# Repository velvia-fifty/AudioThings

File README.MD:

# AudioThings

<div style="display: flex; flex-direction: row;">
 &nbsp;&nbsp;
 &nbsp;&nbsp;  &nbsp;&nbsp; 
</div>

<sup>*I made this for me, maybe you find it helpful?*</sup>

>What is the meaning of life? Are we here only to eat hot chip, shitpost, and make the robot have orgasm?
>
>**No!**
>
>*We do audio, we do thing, we do audio things!*

## Getting the most out of your trip to Cleveland Ohio

When you download this as a ZIP open AudioThings.kicad_pro, this is a panopticon project that contains the main resources and exists to handle some references that are common. Apparently KiCad and I have some foundational disagreement on how to misuse their software; this is primarily because I'm ignorant, but also they have incorrect opinions.

Use Kicad to drill down into other projects.

Or don't, I'm not a cop.

## F.A.Q.

1. Are you OK?
2. Seriously I'm concerned for your wellbeing, is everything alright at home?

🤫

## Navigating this hot mess of a repo

This repo is poorly organized and so am I, here are the main non-project folders.

- [Art](./Art/)
  - Less-than-practical boards that are incomplete.
- [CRIB SHEET](./CRIB%20SHEET/)
  - Things I ~stole~ used for inspiration.
- [docs](./docs/)
  - Audio Things: The Manual: The Webpage: The Source
- [Modules](./Modules/)
  - The stuff that's mostly complete
- [OLD](./OLD/)
  - The trashcan, I sometimes use this to store things
- [res](./res/)
  - Central resource folder containing footprints, 3d models, and other assets.
  - Referenced at ${KIPROJMOD}/../../res/
- [Tools](./Tools/)
  - Hammers, Templates, etc.
- [Workshop](./Workshop/)
  - Half-baked and half-finished boards

### Project Resources

Footprint Library
${KIPRJMOD}/../../res/AT-Footprints.pretty

## I have opinions and they're loud

Opinions are for suckers, we're a big girl, we have convictions (and they're obtuse).

### Maximize Cheap

If we wanted to spend money, we wouldn't pay with our time!

- Boards stay within 100mm x 100mm to get the cheapest per-board costs for small orders
- BOM includes actively produced parts unless there are no other options
- Rely on someone else's scale and use the most common solution in the wrong way

See: [Fab Min-Max Notes](./FAB_NOTES.MD)

### Form Factor Agnostic

- Assume Eurorack
- Assume Backplane
- Assume Stacking
- Assume Standalone

### Your Licensing Model is Bad and You Should Feel Bad

- All work is under copyright, this is not antithetical to the concept of the public domain
  - I mean *all* work, not just this repo.
- What I'm offering is licensed to you under [Creative Commons Attribution-NonCommercial-ShareAlike 4.0 International](https://creativecommons.org/licenses/by-nc-sa/4.0/)
- If you're not an individual, the words "copyright" and "NonCommercial" are very important to both you, me, and a lawyer makes three.
  - Corporations don't have rights.

For how I really feel, see: [LICENSE.MD](./LICENSE.MD)

## Core Features

- Eurorack Compatible
- Backplane preferred but optional
- Daughterboards are assumed (Minium PCB order is 5 after all)

# I took notes here, don't look

m.2
<https://github.com/timonsku/M.2-Card-Footprints/tree/main>

# Universal Faceplate

Universal 6mm opening for jacks and pots

11.5mm between board and face

SJ3-350103A 3.5mm Stereo
<https://www.digikey.com/en/products/detail/same-sky-formerly-cui-devices/SJ3-350103A/24627980>

PTV09 Pots
<https://www.bourns.com/docs/Product-Datasheets/PTV09.pdf>

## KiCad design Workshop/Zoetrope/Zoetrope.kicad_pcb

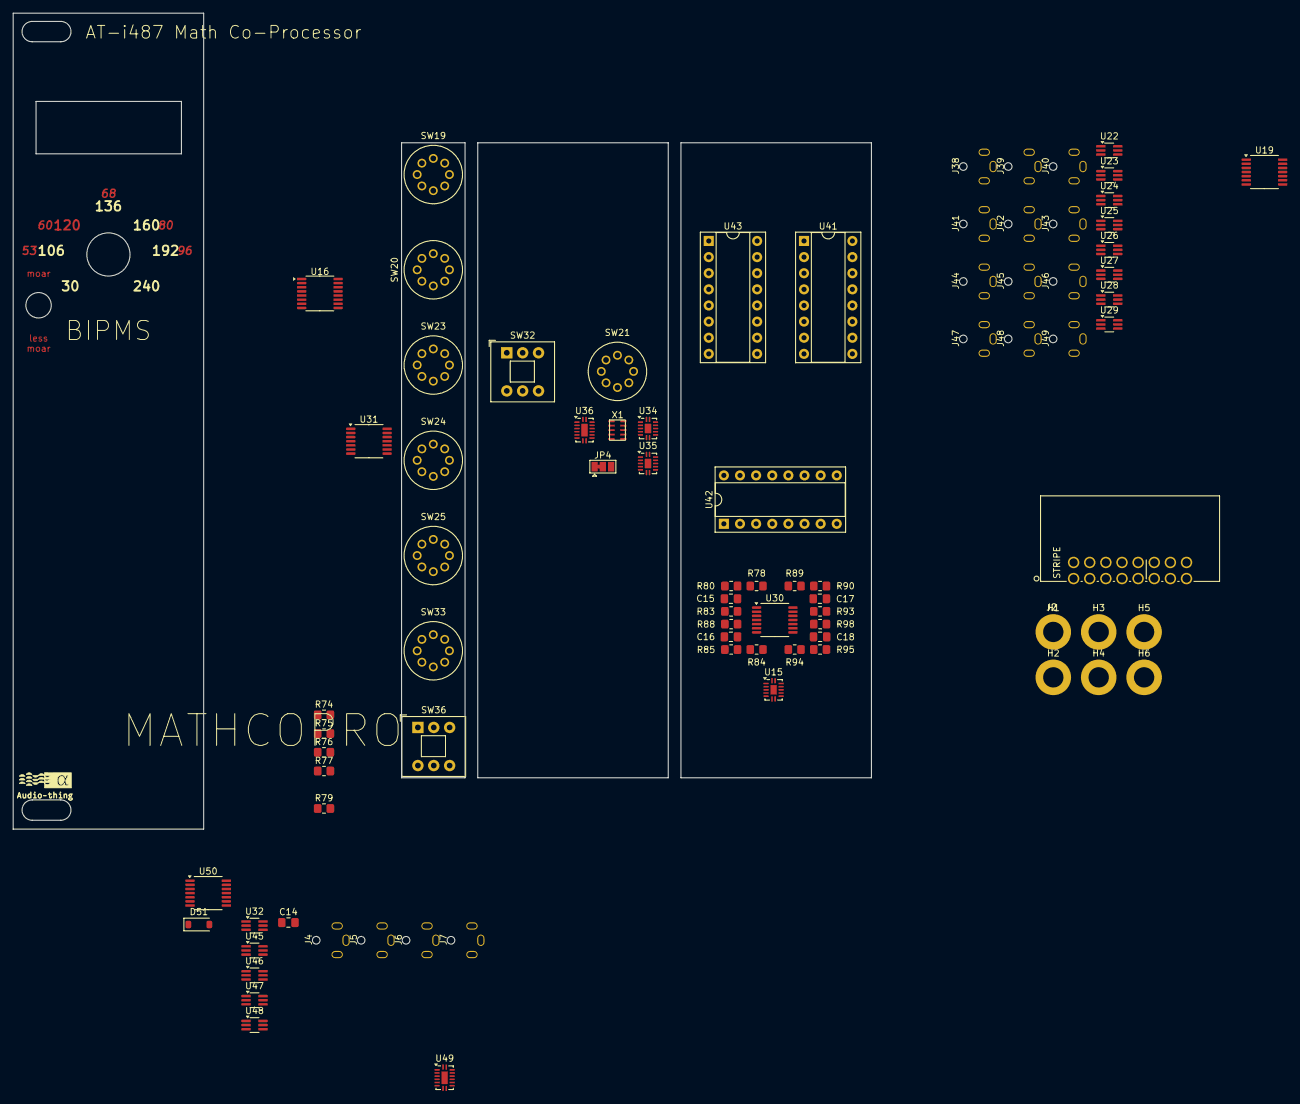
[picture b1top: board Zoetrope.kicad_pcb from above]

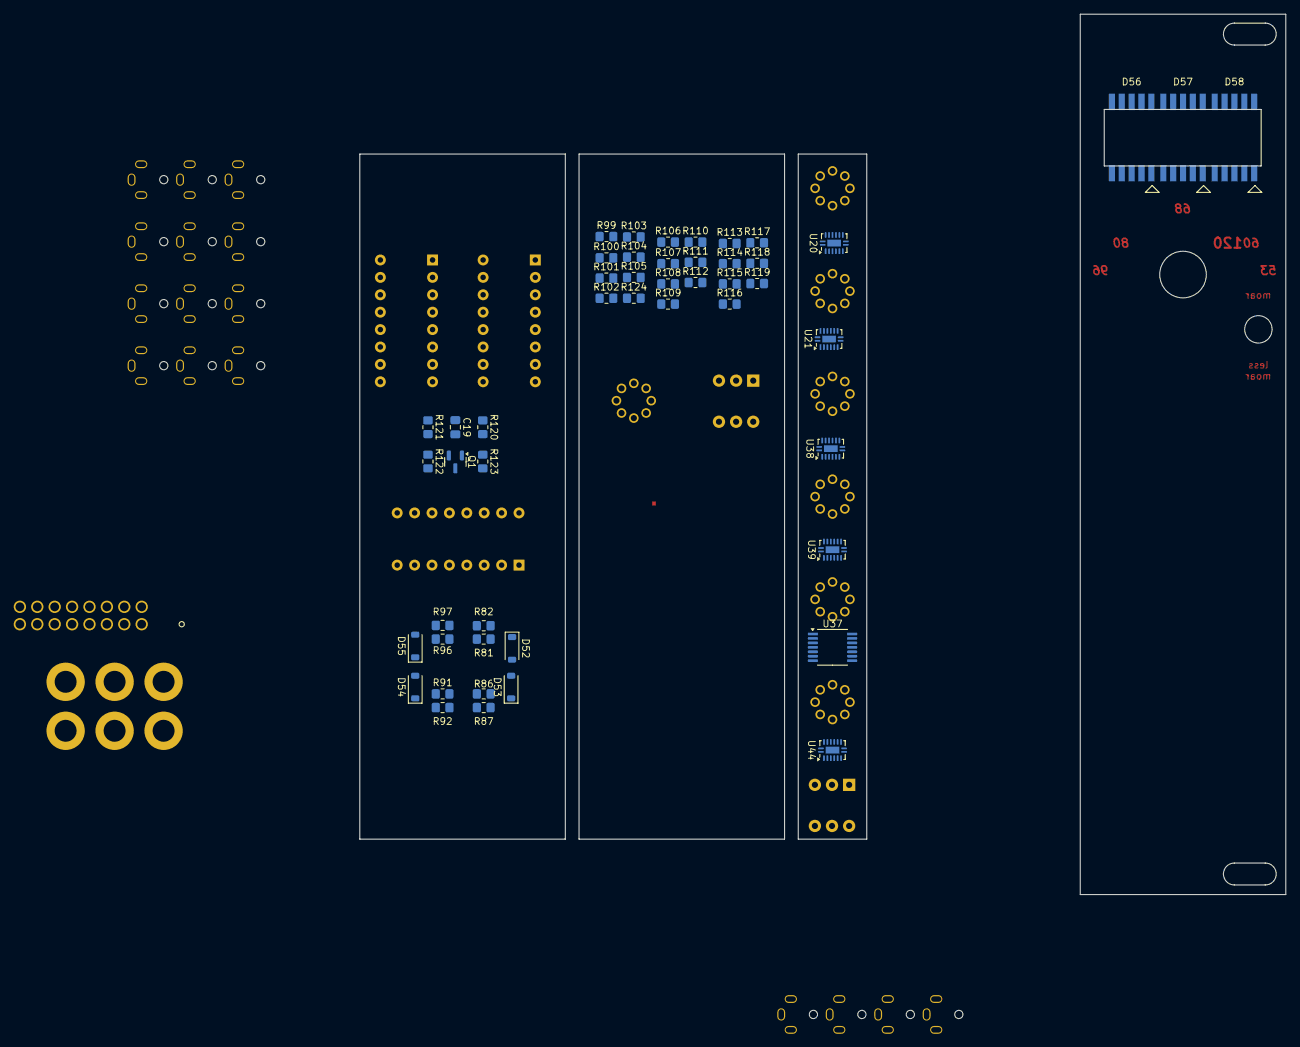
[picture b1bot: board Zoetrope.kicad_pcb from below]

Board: 2 copper layers, 164.4 x 146.6 mm, 132 parts (46 on the bottom side), 159 nets, no tracks yet.

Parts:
C14, C15, C16, C17, C18: 10nf; C_0805_2012Metric_Pad1.18x1.45mm_HandSolder
C19: 100nf; C_0805_2012Metric_Pad1.18x1.45mm_HandSolder
D51, D52, D53, D54, D55: 1N4148W; D_SOD-123
D56: BPM DISP Ones; Reverse Mount WL-S7DS_0.2INCH
D57: BPM DISP Tens; Reverse Mount WL-S7DS_0.2INCH
D58: BPM DISP Hundreds; Reverse Mount WL-S7DS_0.2INCH
H1, H2, H3, H4, H5, H6: M3; MountingHole_3.2mm_M3_DIN965_Pad
J2: OPT EURO; EURORACK Right Angle
J4: Bar End Trigger; SJ3
J5: Beat Clock Out; SJ3
J6: Phrase End Trigger; SJ3
J7: Gate In - Bank A; SJ3
J38: 1/2 Trigger; SJ3
J39: 1/4 Trigger; SJ3
J40: 1/8 Trigger; SJ3
J41: 1/16 Trigger; SJ3
J42: 1/2 Front Gate; SJ3
J43: 1/4 Front Gate; SJ3
J44: 1/8 Front Gate; SJ3
J45: 1/16 Front Gate; SJ3
J46: 1/2 Back Gate; SJ3
J47: 1/4 Back Gate; SJ3
J48: 1/8 Back Gate; SJ3
J49: 1/16 Back Gate; SJ3
JP4: SET BPM Upper; SolderJumper-3_P1.3mm_Bridged12_Pad1.0x1.5mm
Q1: MMBT2222A; SOT-23
R74, R77, R78, R83, R84, R88, R89, R93, R94, R98: 100k; R_0805_2012Metric_Pad1.20x1.40mm_HandSolder
R75, R81, R86, R91, R96: 2.7k; R_0805_2012Metric_Pad1.20x1.40mm_HandSolder
R76, R82, R87, R92, R97: 2.2k; R_0805_2012Metric_Pad1.20x1.40mm_HandSolder
R79, R80, R85, R90, R95, R121: 1k; R_0805_2012Metric_Pad1.20x1.40mm_HandSolder
R99, R100, R101, R102, R103, R104, R105, R106, R107, R108, R109, R110, R111, R112, R113, R114, R115, R116, R117, R118, R119, R124: 150R; R_0805_2012Metric_Pad1.20x1.40mm_HandSolder
R120: 3k3; R_0805_2012Metric_Pad1.20x1.40mm_HandSolder
R122: 20k; R_0805_2012Metric_Pad1.20x1.40mm_HandSolder
R123: 2k; R_0805_2012Metric_Pad1.20x1.40mm_HandSolder
SW19: Bar Length _{Coarse}; RM-SWITCH
SW20, SW23, SW24, SW25: Bar Length _{Cont}; RM-SWITCH
SW21: BPM _{Coarse}; RM-SWITCH
SW32: BPM Range; SW_Push_2P2T_Toggle_CK_PVA2OAH5xxxxxxV2
SW33: Phrase Length; RM-SWITCH
SW36: Single Bar; SW_Push_2P2T_Toggle_CK_PVA2OAH5xxxxxxV2
U15, U34, U35: NEX 74HC393BQ,115; DHVQFN-14-1EP_2.5x3mm_P0.5mm_EP1x1.5mm
U16: 40106; TSSOP-16_4.4x5mm_P0.65mm
U19, U37, U50: 74HC08; TSSOP-14_4.4x5mm_P0.65mm
U20, U21, U36, U38, U39, U44, U49: 4017; DHVQFN-16-1EP_2.5x3.5mm_P0.5mm_EP1x2mm
U22, U23, U24, U25, U26, U27, U28, U29, U32, U45, U46, U47, U48: 74LVC1G3157; SOT-363_SC-70-6_Handsoldering
U30, U31: TL074; TSSOP-14_4.4x5mm_P0.65mm
U41, U42, U43: 40110; DIP-16_W7.62mm_Socket
X1: TG-3541CE

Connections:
1 Count: U20.3 (Q0), U21.15 (Reset)
2 Count: SW19.2, U20.2 (Q1), U22.3
3 Count: SW19.3, U20.4 (Q2), U23.3
4 Count: SW19.1, U20.7 (Q3), U24.3
5 Count: SW20.1, U19.5, U20.10 (Q4), U25.3
6 Count: SW19.4, U20.1 (Q5), U29.3
7 Count: SW20.2, U19.6, U20.5 (Q6), U28.3
8 Count: U20.6 (Q7), U27.3
9 Count: SW19.5, U20.9 (Q8), U26.3
10 Count: SW20.3, U21.2 (Q1), U22.1
11 Count: SW20.4, U21.4 (Q2), U23.1
12 Count: SW19.6, U21.7 (Q3), U24.1
13 Count: SW23.1, U21.10 (Q4), U25.1
14 Count: SW23.2, U21.1 (Q5), U29.1
15 Count: SW23.3, U21.5 (Q6), U28.1
16 Count: SW23.4, U21.6 (Q7), U27.1
16th Trigger: J41.T, R96.2, R97.2
17 Count: SW23.5, U21.9 (Q8), U26.1
18 Count: SW23.6, U38.2 (Q1)
19 Count: SW23.7, U38.4 (Q2)
20 Count: SW24.1, U38.7 (Q3)
21 Count: SW24.2, U38.10 (Q4)
22 Count: SW24.3, U38.1 (Q5)
23 Count: SW24.4, U38.5 (Q6)
24 Count: SW24.5, U38.6 (Q7)
25 Count: SW24.6, U38.9 (Q8)
27 Count: SW25.1, U39.4 (Q2)
28 Count: SW25.2, U39.7 (Q3)
29 Count: SW25.3, U39.10 (Q4)
30 Count: SW25.4, U39.1 (Q5)
30_{BPM}: C19.2, R120.2, R123.1, SW21.7, U35.8 (Q3), U41.6 (LE), U42.6 (LE), U43.6 (LE)
31 Count: SW25.5, U39.5 (Q6)
32 Count: SW25.6, U39.6 (Q7)
33 Count: SW25.7, U39.9 (Q8)
106_{BPM}: SW21.6, U36.9 (Q8)
120_{BPM}: JP4.1 (A), SW21.5, U35.9 (Q2), U35.10 (Q1), U36.6 (Q7)
137_{BPM}: SW21.4, U36.5 (Q6)
160_{BPM}: SW21.3, U36.1 (Q5)
192_{BPM}: SW21.2, U36.10 (Q4)
240_{BPM}: JP4.3 (B), U35.11 (Q0)
+5V: J2.11, J2.12, U15.14 (VCC), U20.16 (VDD), U21.16 (VDD), U34.14 (VCC), U35.14 (VCC), U36.16 (VDD), U38.16 (VDD), U39.16 (VDD), U41.16 (Vdd), U42.16 (Vdd), U43.16 (Vdd), U44.16 (VDD), U49.16 (VDD), X1.1 (OE), X1.2 (VCC), X1.3 (VCC)
+12V: J2.9, J2.10
+12v: R78.2, R84.2, R89.2, R94.2
-12V: J2.1, J2.2
/Bus/CON_CV: J2.13, J2.14
/Bus/CON_GATE: J2.15, J2.16
/SEQ/2.048k Clock: U34.6 (Q3), U34.13 (CP)
/SEQ/8Hz Clock: SW32.3 (C), U35.6 (Q3), U35.13 (CP)
/SEQ/16Hz Clock: SW32.1 (A), U35.5 (Q2)
/SEQ/32.768k Clock: U34.1 (CP), X1.4 (OUT)
/SEQ/128Hz Clock: SW32.6 (C), U34.8 (Q3), U35.1 (CP)
/SEQ/256Hz Clock: SW32.4 (A), U34.9 (Q2)
/SEQ/A1: R99.1, U41.1 (Qa)
/SEQ/A2: R106.1, U42.1 (Qa)
/SEQ/A3: R113.1, U43.1 (Qa)
/SEQ/B1: R100.1, U41.15 (Qb)
/SEQ/B2: R107.1, U42.15 (Qb)
/SEQ/B3: R114.1, U43.15 (Qb)
/SEQ/BPM DISP Clock: Q1.2 (E), R122.2, R124.1, U41.9 (CKu), U42.9 (CKu), U43.9 (CKu)
/SEQ/BPM DISP Reset: C19.1, R121.2, U41.5 (CLR), U42.5 (CLR), U43.5 (CLR)
/SEQ/C1: R101.1, U41.14 (Qc)
/SEQ/C2: R108.1, U42.14 (Qc)
/SEQ/C3: R115.1, U43.14 (Qc)
/SEQ/D1: R102.1, U41.13 (Qd)
/SEQ/D2: R109.1, U42.13 (Qd)
/SEQ/D3: R116.1, U43.13 (Qd)
/SEQ/E1: R103.1, U41.12 (Qe)
/SEQ/E2: R110.1, U42.12 (Qe)
/SEQ/E3: R117.1, U43.12 (Qe)
/SEQ/F1: R104.1, U41.3 (Qf)
/SEQ/F2: R111.1, U42.3 (Qf)
/SEQ/F3: R118.1, U43.3 (Qf)
/SEQ/G1: R105.1, U41.2 (Qg)
/SEQ/G2: R112.1, U42.2 (Qg)
/SEQ/G3: R119.1, U43.2 (Qg)
Bank A - Position: U45.6, U46.6, U47.6, U48.6
Bar: J4.T, SW19.8, U20.15 (Reset), U39.11 (Q9), U44.14 (CLK)
Beat: J5.T, Q1.3 (C), SW21.8, U20.14 (CLK), U36.15 (Reset)
Eighth Bar: SW33.6, U44.6 (Q7)
Eighth Note A: C17.1, J44.T, J48.T, U15.4 (Q1), U15.10 (Q1), U46.1, U46.3
Eighth Tigger: J40.T, R91.2, R92.2
Fifth Bar: SW33.3, U44.10 (Q4)
Fourth Bar: SW33.2, U44.7 (Q3)
GND: D56.3, D57.3, D58.3, J2.3, J2.4, J2.5, J2.6, J2.7, J2.8, J4.S, J5.S, J6.S, J7.S, J38.S, J39.S, J40.S, J41.S, J42.S, J43.S, J44.S, J45.S, J46.S, J47.S, J48.S, J49.S, R74.2, R76.1, R79.1, R80.1, R82.1, R83.1, R85.1, R87.1, R88.1, R90.1, R92.1, R93.1, R95.1, R97.1, R98.1, R120.1, R121.1, R122.1, U15.2 (MR), U15.7 (GND), U15.12 (MR), U20.8 (VSS), U21.8 (VSS), U21.13 (CKEN), U34.2 (MR), U34.7 (GND), U34.12 (MR), U35.2 (MR), U35.7 (GND), U35.12 (MR), U36.8 (VSS), U36.13 (CKEN), U38.8 (VSS), U38.13 (CKEN), U39.8 (VSS), U39.13 (CKEN), U41.4 (~TE), U41.7 (CKd), U41.8 (Vss), U42.4 (~TE), U42.7 (CKd), U42.8 (Vss), U43.4 (~TE), U43.7 (CKd), U43.8 (Vss), U44.8 (VSS), U44.13 (CKEN), U49.8 (VSS), U49.13 (CKEN), X1.5 (GND), X1.7 (GND), X1.8 (GND), X1.9 (GND)
Half Note A: C14.1, C15.1, J42.T, J46.T, U15.6 (Q3), U15.8 (Q3), U48.1, U48.3
Half Trigger: J38.T, R81.2, R82.2
unnamed: D51.2 (A), U31.7
unnamed: D51.1 (K), R75.1
unnamed: D52.2 (A), U30.1
unnamed: D52.1 (K), R81.1
unnamed: D53.2 (A), U30.7
unnamed: D53.1 (K), R86.1
unnamed: D54.2 (A), U30.8
unnamed: D54.1 (K), R91.1
unnamed: D55.2 (A), U30.14
unnamed: D55.1 (K), R96.1
unnamed: D56.1, R103.2
unnamed: D56.2, R102.2
unnamed: D56.4, R101.2
unnamed: D56.5, R124.2
unnamed: D56.6, R100.2
unnamed: D56.7, R99.2
unnamed: D56.9, R104.2
unnamed: D56.10, R105.2
unnamed: D57.1, R110.2
unnamed: D57.2, R109.2
unnamed: D57.4, R108.2
unnamed: D57.6, R107.2
unnamed: D57.7, R106.2
unnamed: D57.9, R111.2
unnamed: D57.10, R112.2
unnamed: D58.1, R117.2
unnamed: D58.2, R116.2
unnamed: D58.4, R115.2
unnamed: D58.6, R114.2
unnamed: D58.7, R113.2
unnamed: D58.9, R118.2
unnamed: D58.10, R119.2
unnamed: U20.11 (Q9), U37.1
unnamed: U21.11 (Q9), U37.4
unnamed: U37.9, U38.11 (Q9)
unnamed: JP4.2 (C), SW21.1
unnamed: Q1.1 (B), R123.2
unnamed: U22.6, U23.6, U24.6, U25.6, U26.6, U27.6, U28.6, U29.6
unnamed: SW19.7, SW20.8
unnamed: SW20.5, SW23.8
unnamed: SW20.6, SW24.8
unnamed: SW20.7, SW25.8
unnamed: SW32.2 (B), U36.14 (CLK)
unnamed: SW32.5 (B), U15.1 (CP), U16.1
unnamed: SW33.8, SW36.3 (C)
unnamed: U15.13 (CP), U16.2
unnamed: U20.13 (CKEN), U37.2, U37.5, U37.10
unnamed: U21.14 (CLK), U37.3
unnamed: U21.3 (Q0), U38.15 (Reset)
unnamed: C15.2, R83.2, U30.3 (+)
unnamed: R78.1, R80.2, U30.2 (-)
unnamed: C16.2, R88.2, U30.5 (+)
unnamed: R84.1, R85.2, U30.6 (-)
unnamed: C17.2, R93.2, U30.10 (+)
unnamed: R89.1, R90.2, U30.9 (-)
unnamed: C18.2, R98.2, U30.12 (+)
unnamed: R94.1, R95.2, U30.13 (-)
unnamed: R77.1, R79.2, U31.5 (+)
unnamed: C14.2, R74.1, U31.6 (-)
unnamed: U37.6, U38.14 (CLK)
unnamed: U38.3 (Q0), U39.15 (Reset)
unnamed: U37.8, U39.14 (CLK)
unnamed: U50.2, U50.6
Phrase: J6.T, SW36.2 (B), U44.15 (Reset)
Phrase Reset: SW33.7, U44.9 (Q8)
Quarter Note A: C16.1, J43.T, J47.T, U15.5 (Q2), U15.9 (Q2), U47.1, U47.3
Quarter Trigger: J39.T, R86.2, R87.2
Second Bar: SW36.1 (A), U44.2 (Q1)
Seventh Bar: SW33.5, U44.5 (Q6)
Sixteenth Note A: C18.1, J45.T, J49.T, U15.3 (Q0), U15.11 (Q0), U45.1, U45.3
Sixth Bar: SW33.4, U44.1 (Q5)
Third Bar: SW33.1, U44.4 (Q2)
Whole Trigger: R75.2, R76.2

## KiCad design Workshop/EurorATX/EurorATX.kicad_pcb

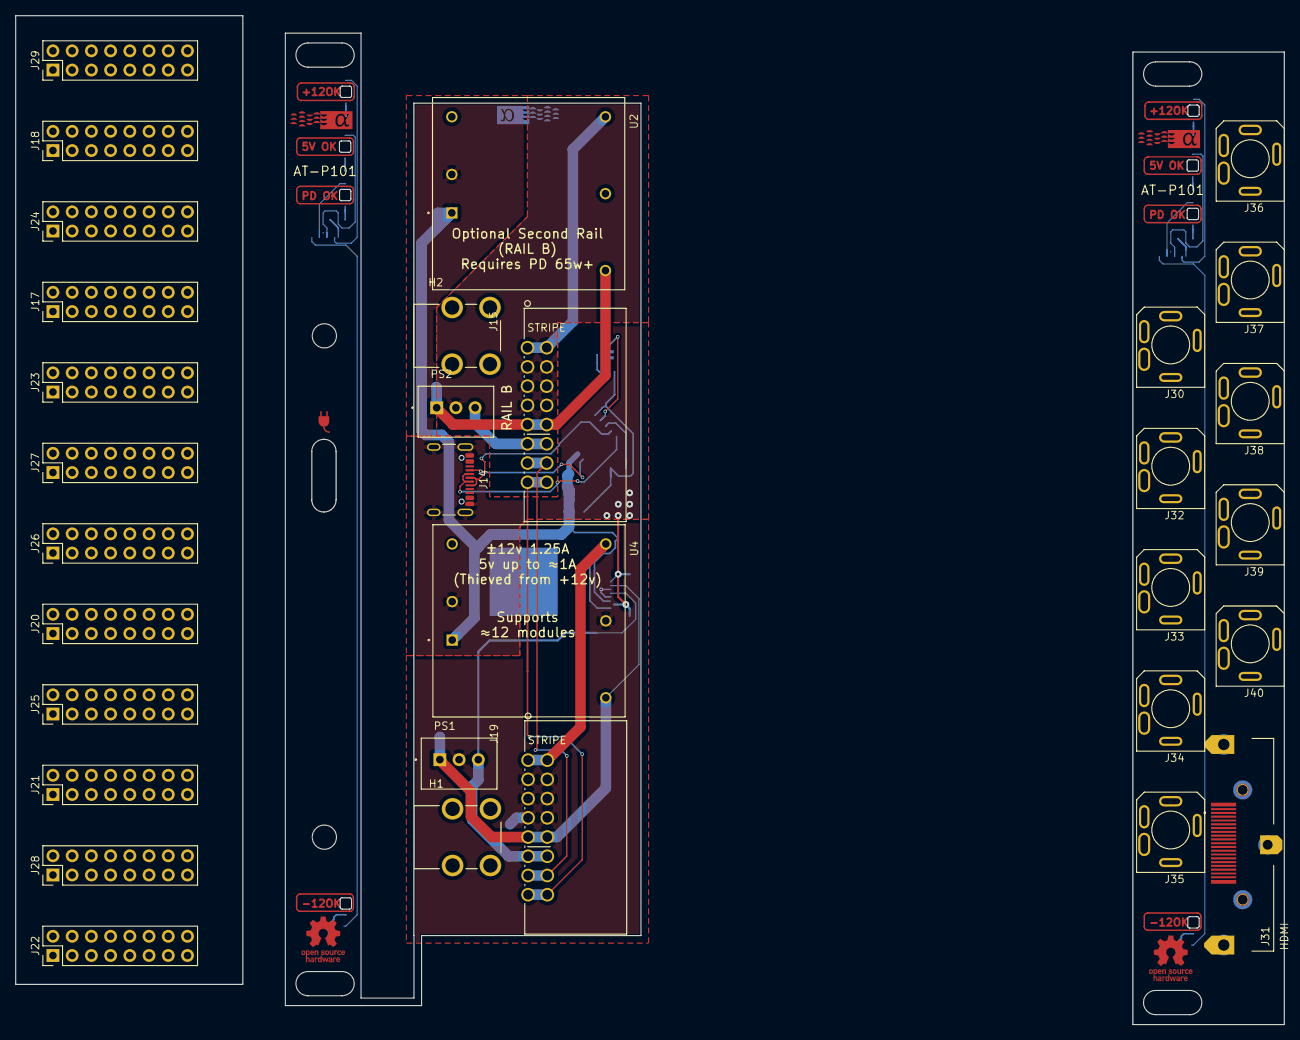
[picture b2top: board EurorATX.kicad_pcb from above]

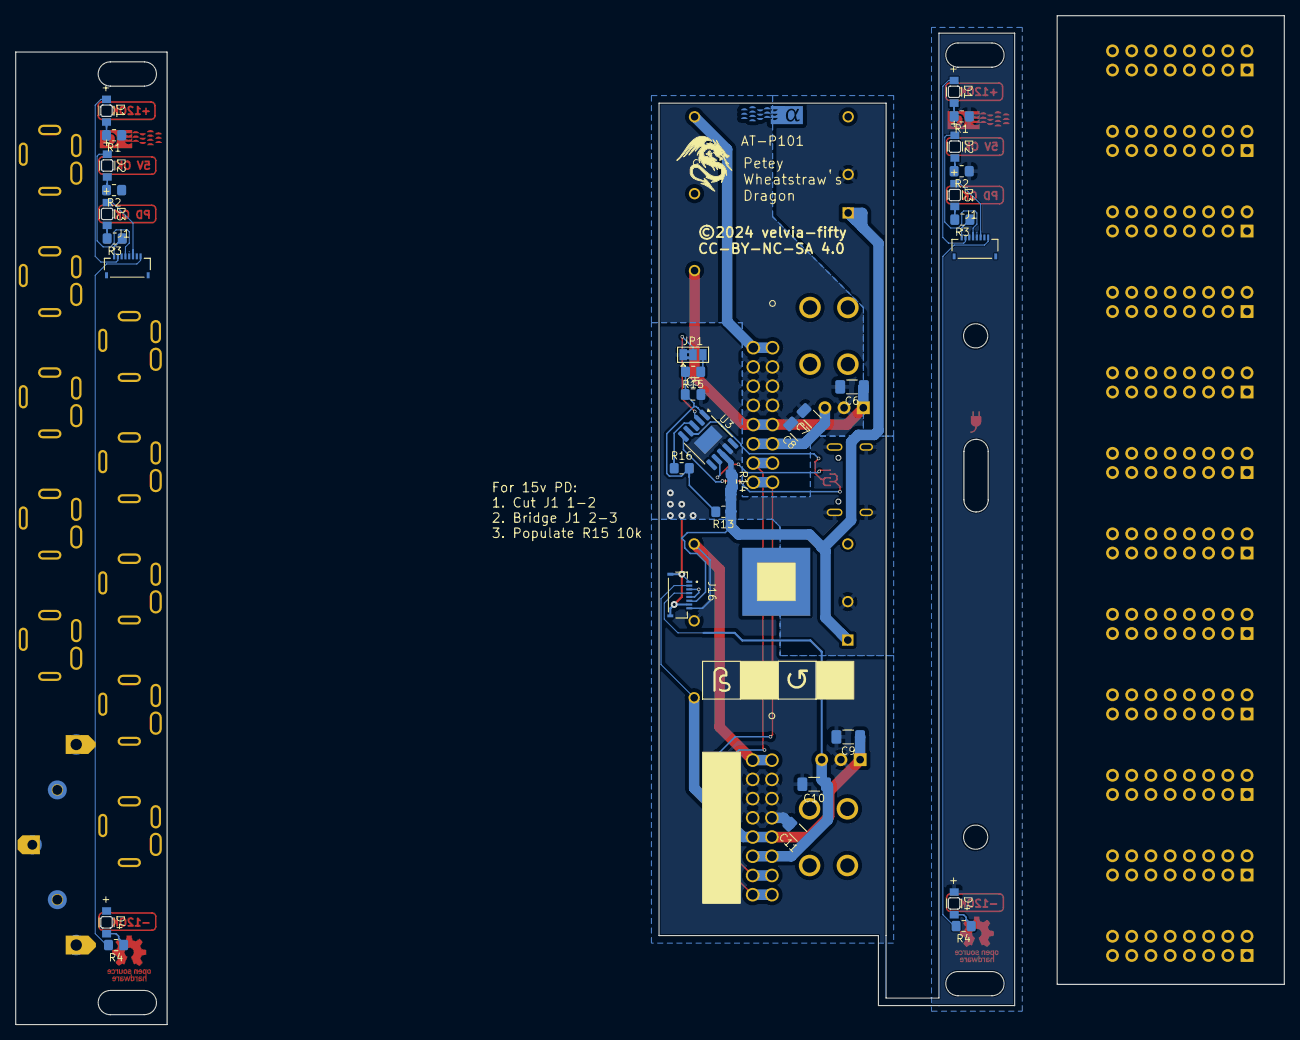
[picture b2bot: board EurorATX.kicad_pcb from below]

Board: 2 copper layers, 167.6 x 133.3 mm, 72 parts (25 on the bottom side), 38 nets.

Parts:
C5: 1uF; C_0805_2012Metric_Pad1.18x1.45mm_HandSolder
C6, C9: 10uF; C_1206_3216Metric_Pad1.33x1.80mm_HandSolder
C7, C8, C10, C11: 47uF; C_1206_3216Metric_Pad1.33x1.80mm_HandSolder
CUT1: SYM_Flash_Small; USB C Cutout - PD
D1, D1#2: LED (Red); WL-SMRD_1205
D2, D2#2: LED (Yellow); WL-SMRD_1205
D3, D3#2: LED (Green); WL-SMRD_1205
D4, D4#2: LED (Blue); WL-SMRD_1205
GFX1: FRONT PANEL AT LOGO; at-logo-cu
GFX2, GFX2#2: FRONT PANEL OSHW; OSHW-Logo_5.7x6mm_Copper
GFX3, GFX3#2: FRONT PANEL AT LOGO; at-logo-ex-cu
H1, H2: M3; Keystone 7760 - M3 RA Mount
H3, H4: M3; MountingHole_3.2mm_M3_DIN965
J1, J1#2: FRONT PANEL MAGIC; AMPHENOL_F33B-1A7Q1-E8C08
J14: USB C PD IN; USB_C_Receptacle_GCT_USB4105-xx-A_16P_TopMnt_Horizontal
J15: EURO CH 2; EURORACK Right Angle
J16: MAINBOARD MAGIC; AMPHENOL_F33B-1A7Q1-E8C08
J17, J18, J20, J21, J22, J23, J24, J25, J26, J27, J28, J29: EURO BUS; PinHeader_2x08_P2.54mm_Vertical_SHROUDED
J19: EURO CH 1; EURORACK Right Angle
J30, J32, J33, J34, J35, J36, J37, J38, J39, J40: AudioJack3_SwitchT; SJ3-3505
J31: HDMI; AMPHENOL_10078837-001LF
JP1: 12v/15v; SolderJumper-3_P1.3mm_Bridged2Bar12_Pad1.0x1.5mm
PS1, PS2: TPSM84205EAB; CONV_TPSM84205EAB
R1, R1#2: 500R; R_0805_2012Metric_Pad1.20x1.40mm_HandSolder
R2, R2#2: 150R; R_0805_2012Metric_Pad1.20x1.40mm_HandSolder
R3, R3#2, R4, R4#2: 500; R_0805_2012Metric_Pad1.20x1.40mm_HandSolder
R13: 1k; R_0805_2012Metric_Pad1.20x1.40mm_HandSolder
R14, R15, R16: 10k; R_0805_2012Metric_Pad1.20x1.40mm_HandSolder
U2: 30 Watt Rail 2; MODULE_JSM2512D12
U3: CH224K; SSOP-10-1EP_3.9x4.9mm_P1mm_EP2.1x3.3mm
U4: 30W Rail 1; MODULE_JSM2512D12

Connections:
+5v: C10.1, C11.1, J16.4, J19.11, J19.12, PS1.3 (VOUT)
+5v B: C7.1, C8.1, J15.11, J15.12, PS2.3 (VOUT)
+12v: C9.1, J16.2, J19.9, J19.10, PS1.1 (VIN), U4.3 (+VOUT)
+12v B: C6.1, J15.9, J15.10, PS2.1 (VIN), U2.3 (+VOUT)
-12v: J16.8, J19.1, J19.2, U4.5 (-VOUT)
-12v B: J15.1, J15.2, U2.5 (-VOUT)
/PDPSU/CON_CV: J15.13, J15.14, J19.13, J19.14
/PDPSU/CON_GATE: J15.15, J15.16, J19.15, J19.16
/PDPSU/D+: J14.A6 (D+), J14.B6 (D+), U3.4 (D+)
/PDPSU/D-: J14.A7 (D-), J14.B7 (D-), U3.5 (D-)
/PDPSU/VBUS: J14.A4 (VBUS), J14.A9 (VBUS), J14.B4 (VBUS), J14.B9 (VBUS), R13.1, R14.1, R14.2, U2.1 (+VIN), U3.8 (VBUS), U4.1 (+VIN)
/PDU/BUS +5V: J17.11, J17.12, J18.11, J18.12, J20.11, J20.12, J21.11, J21.12, J22.11, J22.12, J23.11, J23.12, J24.11, J24.12, J25.11, J25.12, J26.11, J26.12, J27.11, J27.12, J28.11, J28.12, J29.11, J29.12
/PDU/BUS +12V: J17.9, J17.10, J18.9, J18.10, J20.9, J20.10, J21.9, J21.10, J22.9, J22.10, J23.9, J23.10, J24.9, J24.10, J25.9, J25.10, J26.9, J26.10, J27.9, J27.10, J28.9, J28.10, J29.9, J29.10
/PDU/BUS -12V: J17.1, J17.2, J18.1, J18.2, J20.1, J20.2, J21.1, J21.2, J22.1, J22.2, J23.1, J23.2, J24.1, J24.2, J25.1, J25.2, J26.1, J26.2, J27.1, J27.2, J28.1, J28.2, J29.1, J29.2
/PDU/BUS COM: J17.3, J17.4, J17.5, J17.6, J17.7, J17.8, J18.3, J18.4, J18.5, J18.6, J18.7, J18.8, J20.3, J20.4, J20.5, J20.6, J20.7, J20.8, J21.3, J21.4, J21.5, J21.6, J21.7, J21.8, J22.3, J22.4, J22.5, J22.6, J22.7, J22.8, J23.3, J23.4, J23.5, J23.6, J23.7, J23.8, J24.3, J24.4, J24.5, J24.6, J24.7, J24.8, J25.3, J25.4, J25.5, J25.6, J25.7, J25.8, J26.3, J26.4, J26.5, J26.6, J26.7, J26.8, J27.3, J27.4, J27.5, J27.6, J27.7, J27.8, J28.3, J28.4, J28.5, J28.6, J28.7, J28.8, J29.3, J29.4, J29.5, J29.6, J29.7, J29.8
/PDU/BUS_CON_CV: J17.13, J17.14, J18.13, J18.14, J20.13, J20.14, J21.13, J21.14, J22.13, J22.14, J23.13, J23.14, J24.13, J24.14, J25.13, J25.14, J26.13, J26.14, J27.13, J27.14, J28.13, J28.14, J29.13, J29.14
/PDU/BUS_CON_GATE: J17.15, J17.16, J18.15, J18.16, J20.15, J20.16, J21.15, J21.16, J22.15, J22.16, J23.15, J23.16, J24.15, J24.16, J25.15, J25.16, J26.15, J26.16, J27.15, J27.16, J28.15, J28.16, J29.15, J29.16
COM: C9.2, C10.2, C11.2, J19.3, J19.4, J19.5, J19.6, J19.7, J19.8, PS1.2 (GND), U4.4 (COMMON)
COM B: C6.2, C7.2, C8.2, J15.3, J15.4, J15.5, J15.6, J15.7, J15.8, PS2.2 (GND)
FP COM: D4.2 (A), D4#2.2 (A), J1.3, J1.5, J1#2.3, J1#2.5, R1.1, R1#2.1, R2.1, R2#2.1
FP GND: J1.1, J1.7, J1#2.1, J1#2.7, R3.1, R3#2.1
GND: C5.2, J14.A1 (GND), J14.A12 (GND), J14.B1 (GND), J14.B12 (GND), J14.S1 (SHIELD), J16.SH1, J16.SH2, JP1.1 (A), U2.2 (-VIN), U3.9 (CFG1), U3.11 (GND), U4.2 (-VIN)
LED BLU: J1.8, J1#2.8, R4.2, R4#2.2
LED GRN: D3.2 (A), D3#2.2 (A), J1.6, J1#2.6
LED RED: D1.2 (A), D1#2.2 (A), J1.2, J1#2.2
LED YLW: D2.2 (A), D2#2.2 (A), J1.4, J1#2.4
unnamed: D1.1 (K), D1#2.1 (K), R1.2, R1#2.2
unnamed: D2.1 (K), D2#2.1 (K), R2.2, R2#2.2
unnamed: D3.1 (K), D3#2.1 (K), R3.2, R3#2.2
unnamed: D4.1 (K), D4#2.1 (K), R4.1, R4#2.1
unnamed: J14.A5 (CC1), U3.7 (CC1)
unnamed: J14.B5 (CC2), U3.6 (CC2)
unnamed: JP1.3 (B), R15.1
unnamed: JP1.2 (C), U3.2 (CFG2)
unnamed: R16.1, U3.3 (CFG3)
unnamed: C5.1, R13.2, R15.2, R16.2, U3.1 (VDD)
SM COM: J16.3, J16.5
SM GND: J16.1, J16.7

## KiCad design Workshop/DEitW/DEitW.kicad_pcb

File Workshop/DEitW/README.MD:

# Densest Envelope in the West

You know what really chaps my ass? When I spend hours tweaking a knob and FINALLY It's just right, It never needs to be touched again because the demons in charge of such things will prevent me from getting it _just right_ ever again.

_**AND THEN THE KNOB HAS THE AUDACITY TO CONTINUE TO EXIST!? LIKE COME ON!!!**_

## What problem are you trying to solve?

I think I was pretty clear honestly...

Sometimes that **[redacted]** I just popped wasn't **[redacted]** and if I'm gonna be tweaking for the next 32 hours I don't want to lose all that progress. **SIX** ADSR Envelopes, **TWELVE** turns per pot; I can't math good but that's got to be at least a few hundred unique types of bloop per bleep.

Did I mention that the interface is offboard, cause the actual mailroom plops onto whatever board needs it most (or is handy); it even has the common decency to give you the option for internal trimpots, no panel space needed. _(Oh, and I stole the circuit from René Schmitz so it chooches)

But, I get it, you want to fondle those robot nips whenever you damn well please! It's a standard control interface my dude, if you don't care about density use big girl pots. I literally cannot stop you (but I can judge you)

The point is other modules can wear this as a hat, one of those fancy tiny bullshit hats that the royals wear to cockfights.

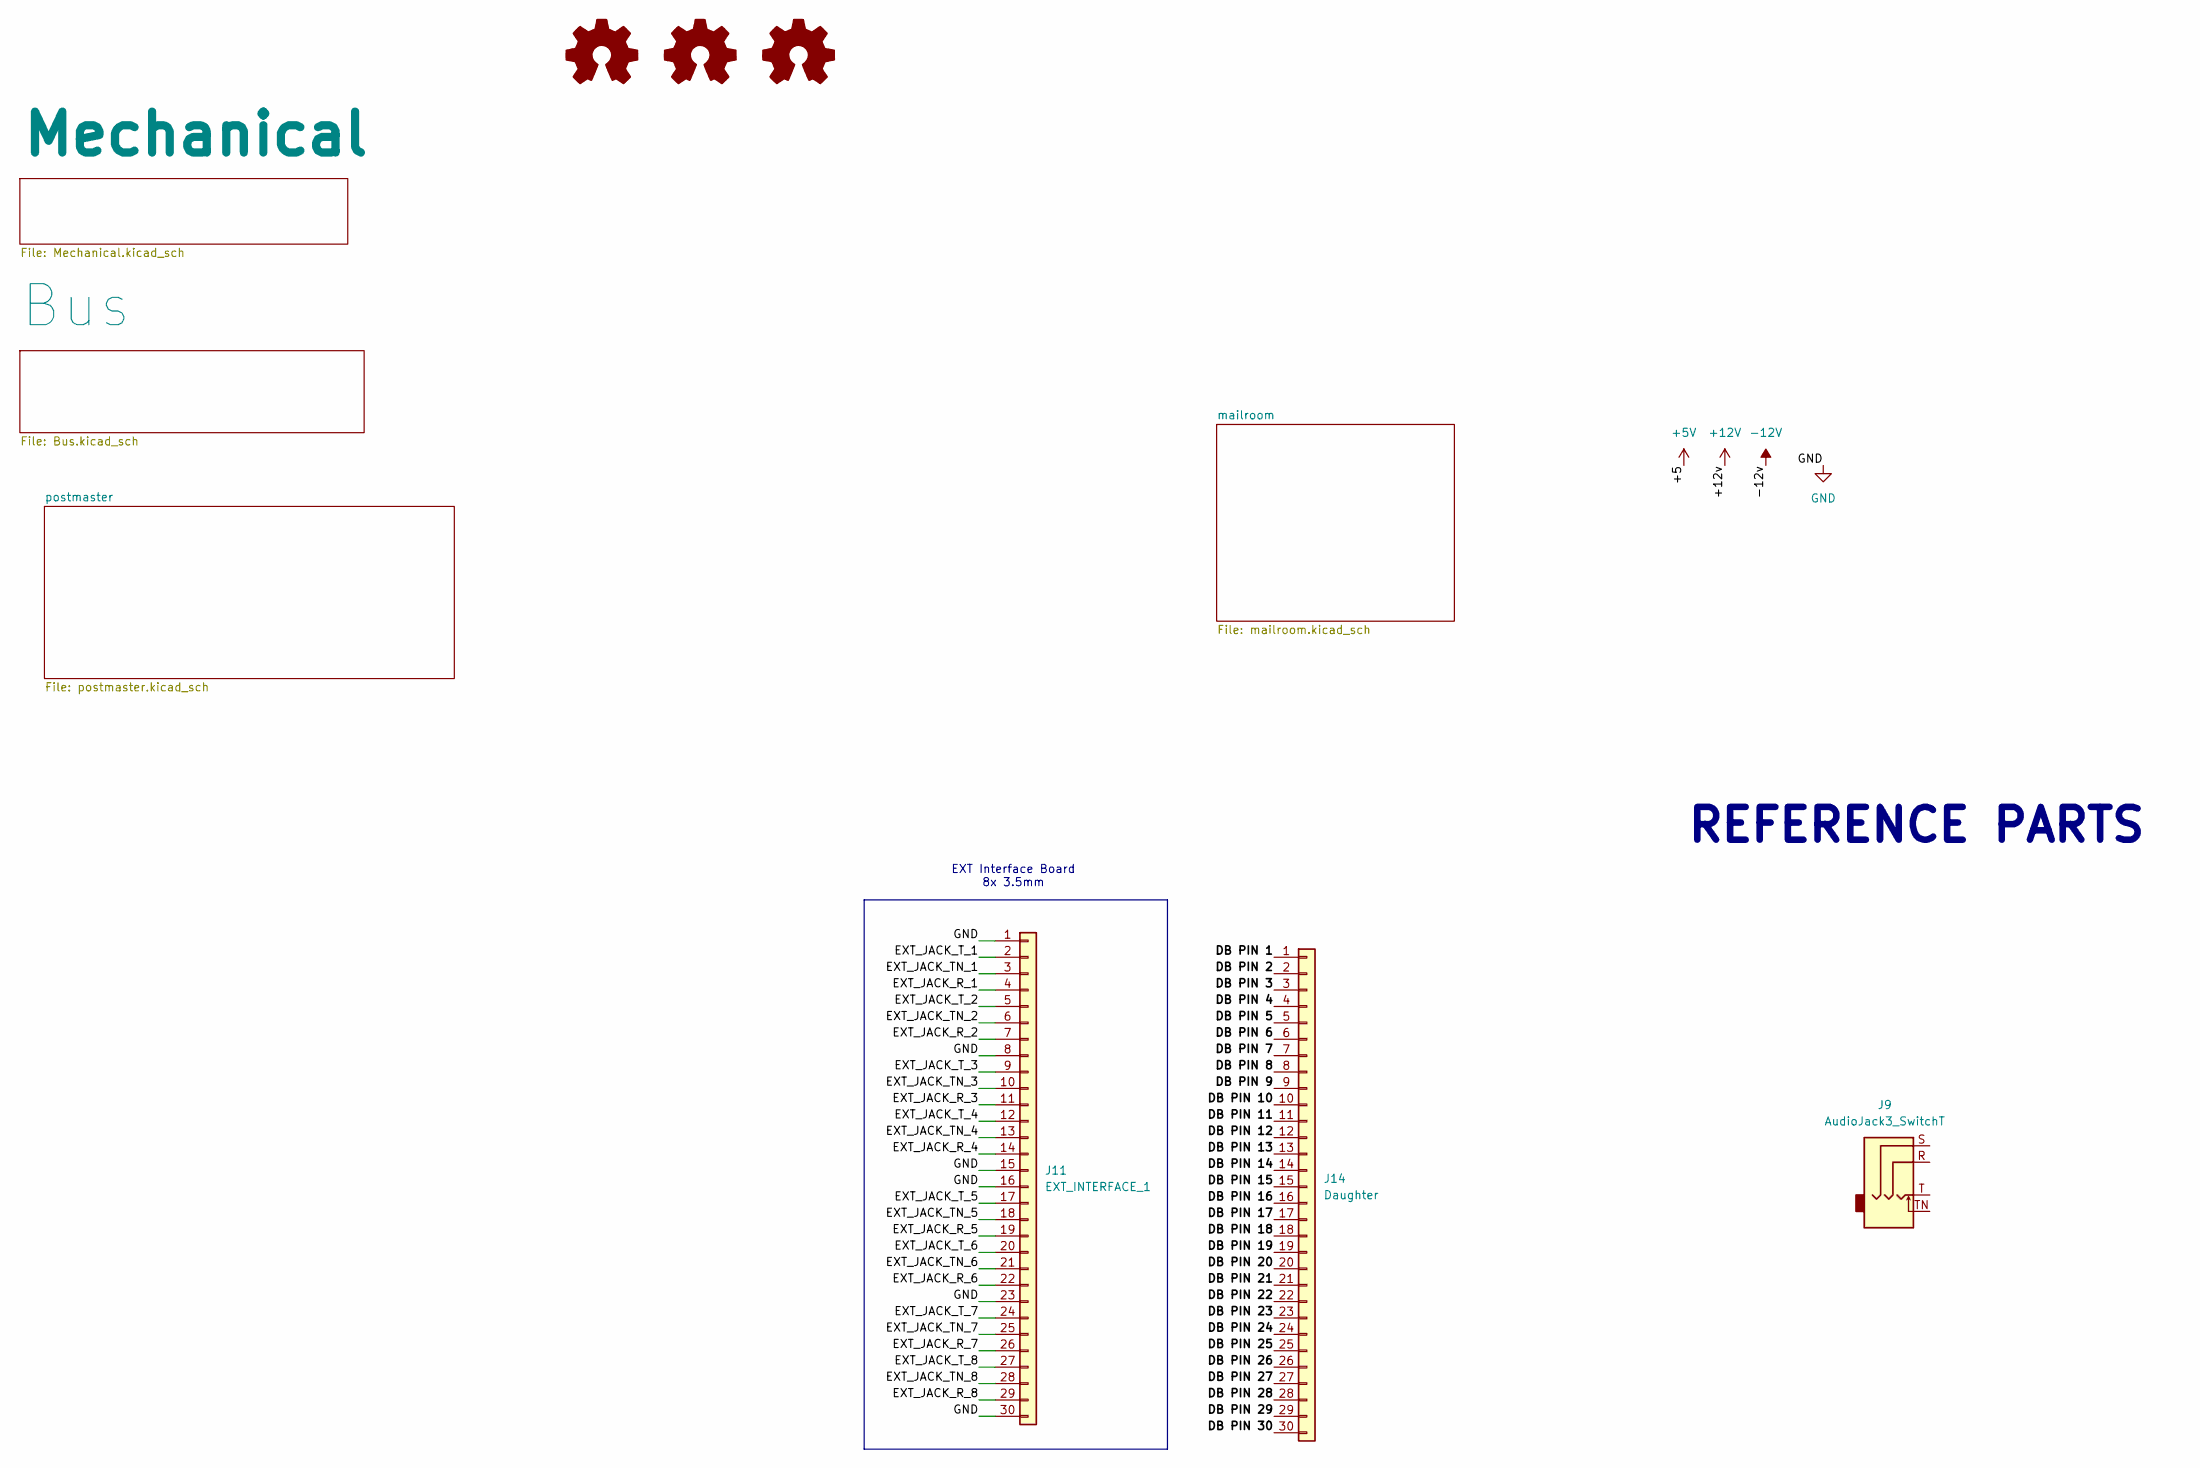
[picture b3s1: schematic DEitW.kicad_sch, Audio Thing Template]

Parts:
J9: AudioJack3_SwitchT; SJ3
J11: EXT_INTERFACE_1; AMPHENOL_SFV30R-4STE1HLF - FFC - 30 RA
J14: Daughter; AMPHENOL_SFV30R-4STE1HLF - FFC - 30 RA

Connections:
/DB PIN 1: J14.1
/DB PIN 2: J14.2
/DB PIN 3: J14.3
/DB PIN 4: J14.4
/DB PIN 5: J14.5
/DB PIN 6: J14.6
/DB PIN 7: J14.7
/DB PIN 8: J14.8
/DB PIN 9: J14.9
/DB PIN 10: J14.10
/DB PIN 11: J14.11
/DB PIN 12: J14.12
/DB PIN 13: J14.13
/DB PIN 14: J14.14
/DB PIN 15: J14.15
/DB PIN 16: J14.16
/DB PIN 17: J14.17
/DB PIN 18: J14.18
/DB PIN 19: J14.19
/DB PIN 20: J14.20
/DB PIN 21: J14.21
/DB PIN 22: J14.22
/DB PIN 23: J14.23
/DB PIN 24: J14.24
/DB PIN 25: J14.25
/DB PIN 26: J14.26
/DB PIN 27: J14.27
/DB PIN 28: J14.28
/DB PIN 29: J14.29
/DB PIN 30: J14.30
/EXT_JACK_R_1: J11.4
/EXT_JACK_R_2: J11.7
/EXT_JACK_R_3: J11.11
/EXT_JACK_R_4: J11.14
/EXT_JACK_R_5: J11.19
/EXT_JACK_R_6: J11.22
/EXT_JACK_R_7: J11.26
/EXT_JACK_R_8: J11.29
/EXT_JACK_TN_1: J11.3
/EXT_JACK_TN_2: J11.6
/EXT_JACK_TN_3: J11.10
/EXT_JACK_TN_4: J11.13
/EXT_JACK_TN_5: J11.18
/EXT_JACK_TN_6: J11.21
/EXT_JACK_TN_7: J11.25
/EXT_JACK_TN_8: J11.28
/EXT_JACK_T_1: J11.2
/EXT_JACK_T_2: J11.5
/EXT_JACK_T_3: J11.9
/EXT_JACK_T_4: J11.12
/EXT_JACK_T_5: J11.17
/EXT_JACK_T_6: J11.20
/EXT_JACK_T_7: J11.24
/EXT_JACK_T_8: J11.27
GND: J11.1, J11.8, J11.15, J11.16, J11.23, J11.30; also elsewhere on the board

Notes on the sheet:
REFERENCE PARTS
EXT Interface Board 8x 3.5mm

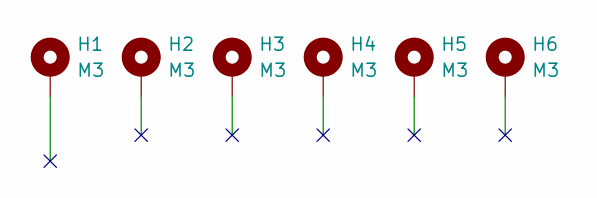
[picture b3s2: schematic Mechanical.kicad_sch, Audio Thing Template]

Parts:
H1, H2, H3, H4, H5, H6: M3; MountingHole_3.2mm_M3_DIN965_Pad

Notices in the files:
Workshop/DEitW/DEitW.kicad_pcb:
©2024 velvia-fifty - CC-BY-NC-SA 4.0
Workshop/EurorATX/EurorATX.kicad_pcb:
CC-BY-NC-SA 4.0
